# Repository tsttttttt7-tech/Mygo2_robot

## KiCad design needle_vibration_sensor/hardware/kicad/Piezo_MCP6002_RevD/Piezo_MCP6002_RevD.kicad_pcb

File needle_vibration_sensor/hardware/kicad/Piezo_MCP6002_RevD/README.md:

# Piezo MCP6002 - Rev D PCB project

Same style as Rev C (self-contained symbols/footprints, routed 2-layer board, DRC, BOM, previews), with the Rev D circuit.

## Open in KiCad
1. Extract the whole ZIP into one folder.
2. Open `Piezo_MCP6002_RevD.kicad_pro` in KiCad 7 or newer.
3. Open the schematic and the PCB from the project tree. If you edit copper, press **B** to refill the zones.

Keep `Piezo_PCB.pretty`, `Piezo_Local.kicad_sym`, `fp-lib-table` and `sym-lib-table` with the project.

## What is included
- Routed two-layer PCB, **48 × 32 mm** (Rev C: 70 × 45 mm), 1.6 mm.
- **All signal tracks on the top layer.** The bottom layer is an unbroken GND plane (best shielding for the high-impedance piezo input). GND pour on top as well.
- 33 components, 0.25 mm tracks, 0.6/0.3 mm vias (8 GND vias next to the SMD GND pads + about 90 stitching vias).
- `Schematic.pdf`, `PCB_top_preview`, `PCB_bottom_preview`, `PCB_routing_preview` (pours hidden), `PCB_assembly` (PNG + PDF).
- `Gerbers_Piezo_MCP6002_RevD.zip`: copper, mask, silk, paste, outline and Excellon drill. Ready to upload to JLCPCB / PCBWay.
- `BOM.csv`, `DRC.txt`, `Validation.txt`, `Connectivity.txt`.

## Changes from Rev C
| | Rev C | Rev D |
|---|---|---|
| Low-pass | 9.9 kHz, E96 values (14.7 k, 6.19 k) | **15 kHz**; every R and C taken from the Ardunic 1206 kits ARD-065066 / ARD-065072 (12k/390k/470p/47p, 33k/200k/470p/33p) |
| C1 (1 µF film input cap) | yes | **removed**: the piezo already blocks DC |
| Input clamp | BAV199 | **BAV99** (same SOT-23 pinout, in stock at Al-Hekmh) |
| Gain | fixed 11 | **11 with JP1 bridged / 44 with JP1 open** (R4 1 k, R3 10 k + R14 33 k) |
| Stability | – | C5 47 pF across the feedback network |
| Outputs | J3 only | **J3 OUT_DC** (ESP32-S3 ADC, via R7/C6) + **J4 OUT_AC** (PCM1808, via C7/R13) |
| Supply filter | R12 22 Ω, C3 47 µF | R12 10 Ω, C3 22 µF |
| Input bias | R2 4.7 MΩ (corner ~3 Hz) | R2 1 MΩ (corner ~16 Hz), the kit's largest value |

## Connectors
| Connector | Pin 1 (square pad) | Pin 2 |
|---|---|---|
| J1 | Piezo ceramic (+) | Piezo brass / GND |
| J2 | Regulated 3.3 V from the ESP32 board | GND |
| J3 | OUT_DC, biased at 1.65 V, to ESP32-S3 GPIO1 | GND |
| J4 | OUT_AC to PCM1808 `L` | GND |

## Assembly notes
- **JP1:** bridge the two pads with solder for gain 11 (start here). Remove the bridge for gain 44.
- U1/U2 are DIP-8 (MCP6002-I/P from Al-Hekmh). Sockets are optional, but they add height (see the housing).
- Filter capacitors C5, C8–C11 are the pF values of the kit (C0G/NP0 dielectric, stable).
- Clean the flux well around the high-impedance nodes: R1/R2/D1/U1 pin 3 (input) and R9 (390k) / R11 (200k) with C9/C11 (filter).
- Three reference labels (C6, R10, R14) had no free silkscreen spot. They are on the assembly (F.Fab) layer: see `PCB_assembly.png`.
- Housing for this board: `../../stl/revD_48x32/` (58 × 42 mm body). Trim the through-hole leads to ≤ 1 mm under the board, because the cover lip leaves 1 mm.

## Validation
KiCad 7.0.11. DRC: **0 violations, 0 unconnected pads, 0 footprint errors**, with the Rev C project rules
(0.2 mm clearance, 0.5 mm copper-to-edge, 0.8 mm silk text). All 79 pad nets and 33 values/footprints match the schematic
netlist exported by KiCad itself (`Validation.txt`). No ERC (not available in kicad-cli 7), and no hardware test yet.

## Regenerate
Everything is produced by scripts in `../tools/` (`design.py` = the netlist):
`bash tools/build_all.sh` (add `--place` to re-run placement). Routing uses a custom 2-layer grid router, then KiCad fills the zones and runs DRC.

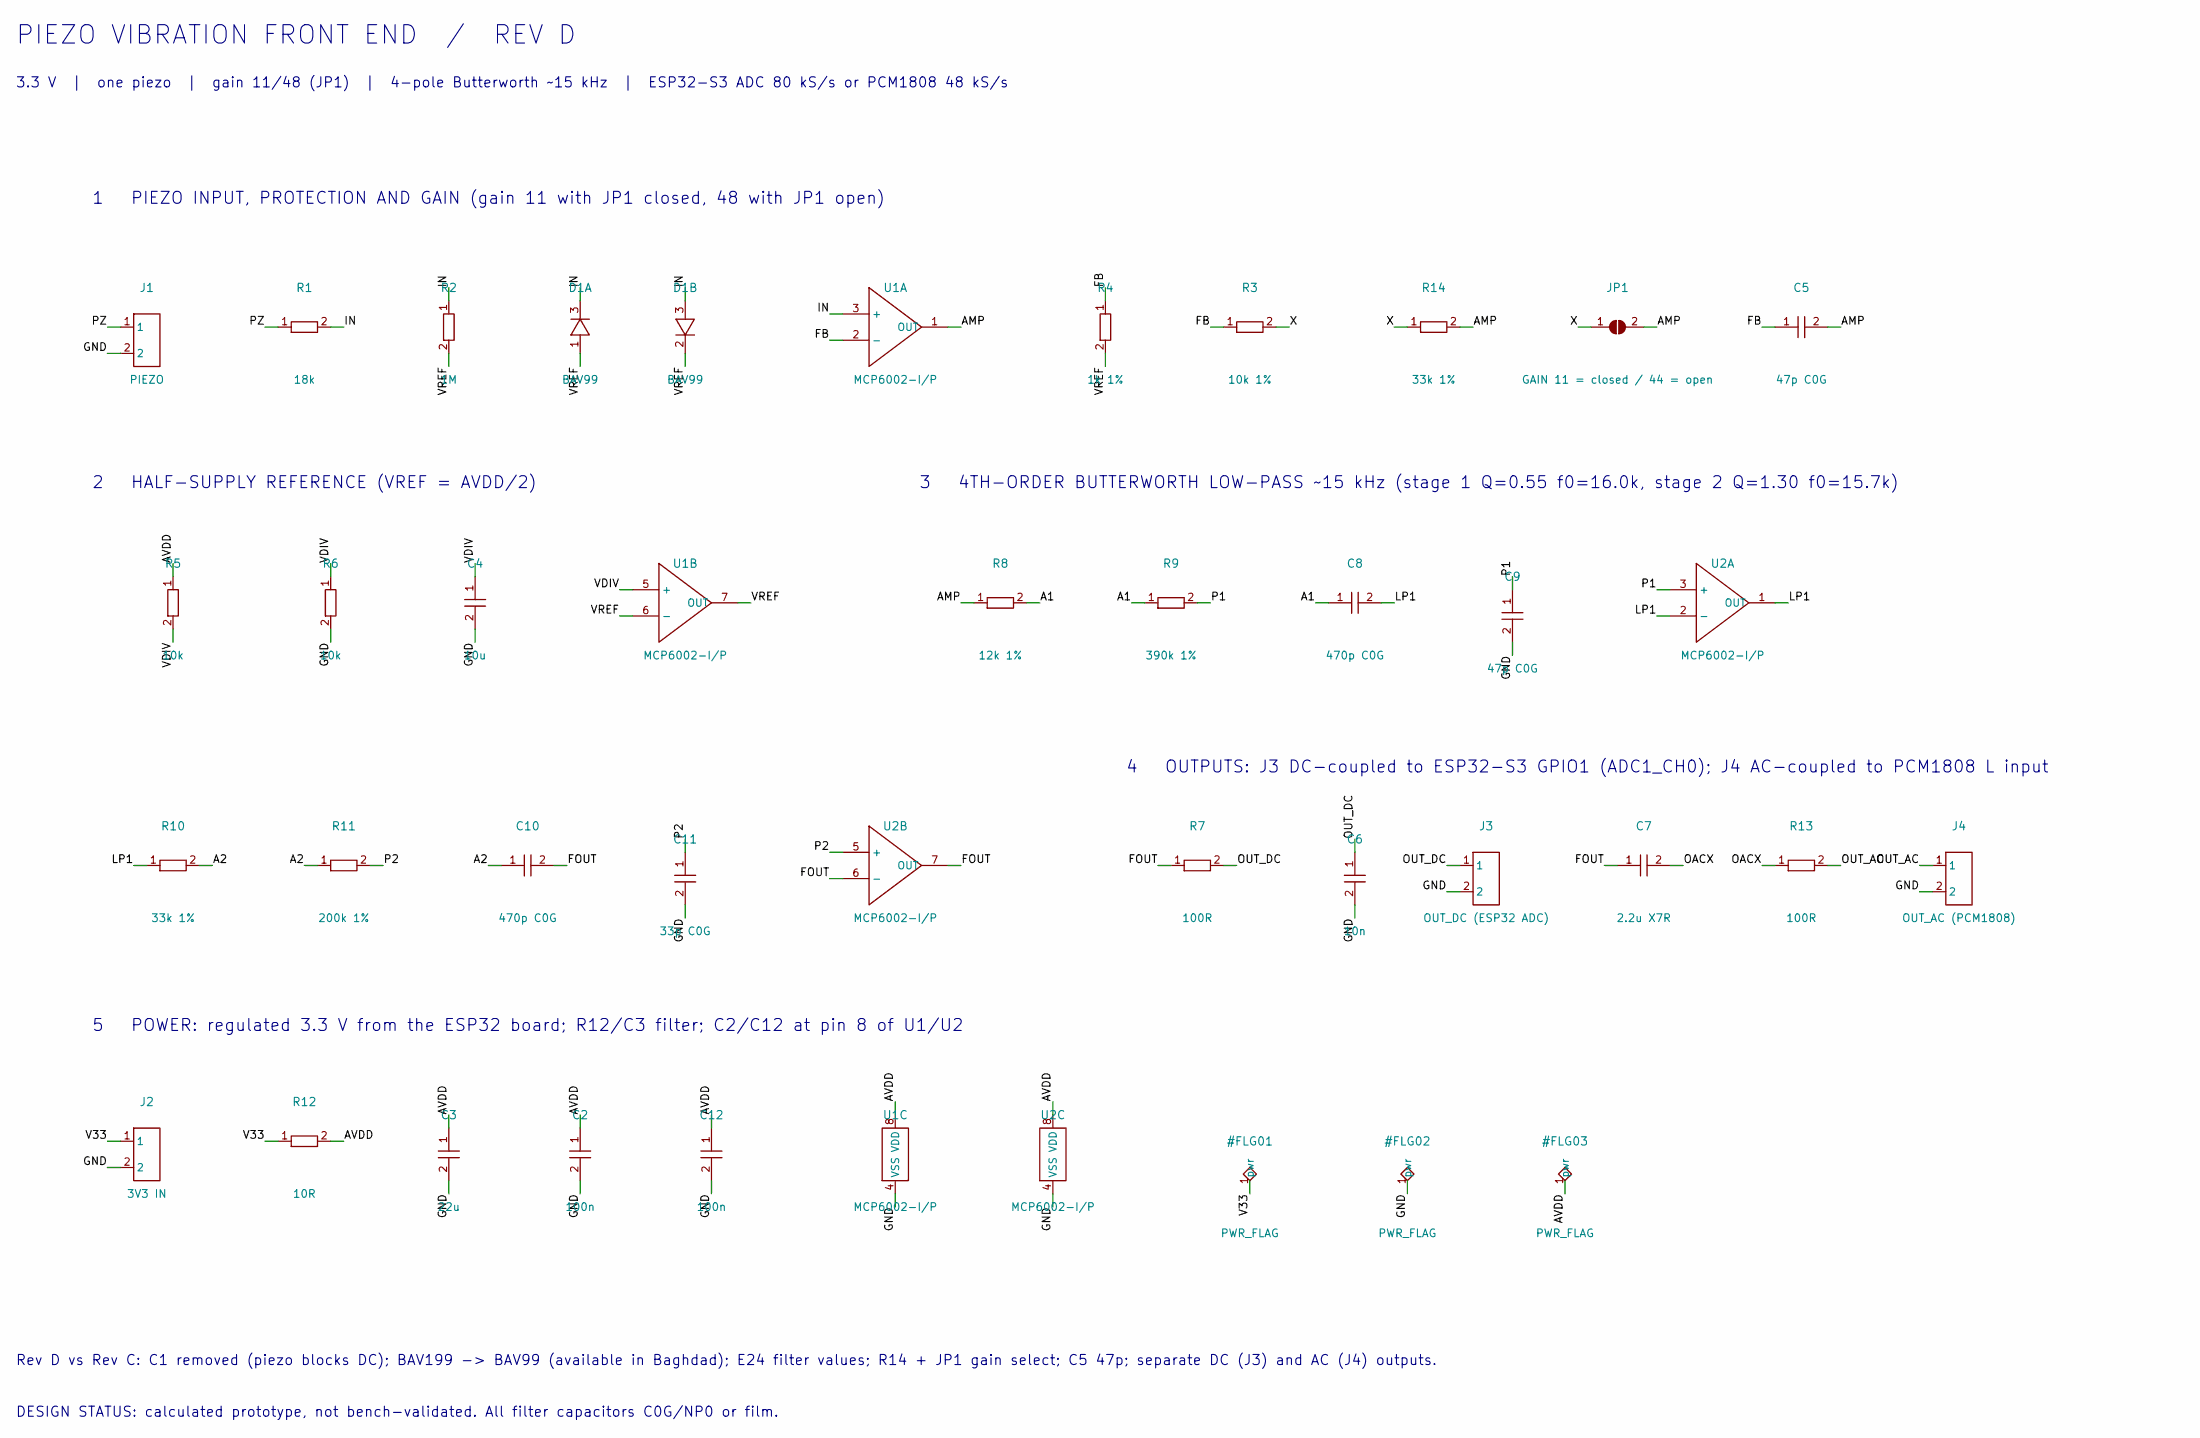
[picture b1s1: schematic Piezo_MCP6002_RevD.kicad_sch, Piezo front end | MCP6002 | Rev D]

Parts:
C2, C12: 100n; C1206
C3: 22u; C1206
C4: 10u; C1206
C5, C9: 47p C0G; C1206
C6: 10n; C1206
C7: 2.2u X7R; C1206
C8, C10: 470p C0G; C1206
C11: 33p C0G; C1206
D1: BAV99; BAV99_SOT23
J1: PIEZO; Header_1x02
J2: 3V3 IN; Header_1x02
J3: OUT_DC (ESP32 ADC); Header_1x02
J4: OUT_AC (PCM1808); Header_1x02
JP1: GAIN 11 = closed / 44 = open; SolderJumper_2
R1: 18k; R1206
R2: 1M; R1206
R3: 10k 1%; R1206
R4: 1k 1%; R1206
R5, R6: 10k; R1206
R7, R13: 100R; R1206
R8: 12k 1%; R1206
R9: 390k 1%; R1206
R10, R14: 33k 1%; R1206
R11: 200k 1%; R1206
R12: 10R; R1206
U1, U2: MCP6002-I/P; DIP8

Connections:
A1: C8.1, R8.2, R9.1
A2: C10.1, R10.2, R11.1
AMP: C5.2, JP1.2, R8.1, R14.2, U1.1 (OUT)
AVDD: C2.1, C3.1, C12.1, R5.1, R12.2, U1.8 (VDD), U2.8 (VDD)
FB: C5.1, R3.1, R4.1, U1.2 (-)
FOUT: C7.1, C10.2, R7.1, U2.6 (-), U2.7 (OUT)
GND: C2.2, C3.2, C4.2, C6.2, C9.2, C11.2, C12.2, J1.2, J2.2, J3.2, J4.2, R6.2, U1.4 (VSS), U2.4 (VSS)
IN: D1.3 (K1/A2), R1.2, R2.1, U1.3 (+)
LP1: C8.2, R10.1, U2.1 (OUT), U2.2 (-)
OACX: C7.2, R13.1
OUT_AC: J4.1, R13.2
OUT_DC: C6.1, J3.1, R7.2
P1: C9.1, R9.2, U2.3 (+)
P2: C11.1, R11.2, U2.5 (+)
PZ: J1.1, R1.1
V33: J2.1, R12.1
VDIV: C4.1, R5.2, R6.1, U1.5 (+)
VREF: D1.1 (A1), D1.2 (K2), R2.2, R4.2, U1.6 (-), U1.7 (OUT)
X: JP1.1, R3.2, R14.1

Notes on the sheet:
1 PIEZO INPUT, PROTECTION AND GAIN (gain 11 with JP1 closed, 48 with JP1 open)
2 HALF-SUPPLY REFERENCE (VREF = AVDD/2)
3 4TH-ORDER BUTTERWORTH LOW-PASS ~15 kHz (stage 1 Q=0.55 f0=16.0k, stage 2 Q=1.30 f0=15.7k)
4 OUTPUTS: J3 DC-coupled to ESP32-S3 GPIO1 (ADC1_CH0); J4 AC-coupled to PCM1808 L input
5 POWER: regulated 3.3 V from the ESP32 board; R12/C3 filter; C2/C12 at pin 8 of U1/U2
PIEZO VIBRATION FRONT END / REV D
3.3 V | one piezo | gain 11/48 (JP1) | 4-pole Butterworth ~15 kHz | ESP32-S3 ADC 80 kS/s or PCM1808 48 kS/s
Rev D vs Rev C: C1 removed (piezo blocks DC); BAV199 -> BAV99 (available in Baghdad); E24 filter values; R14 + JP1 gain select; C5 47p; separate DC (J3) and AC (J4) outputs.
DESIGN STATUS: calculated prototype, not bench-validated. All filter capacitors C0G/NP0 or film.

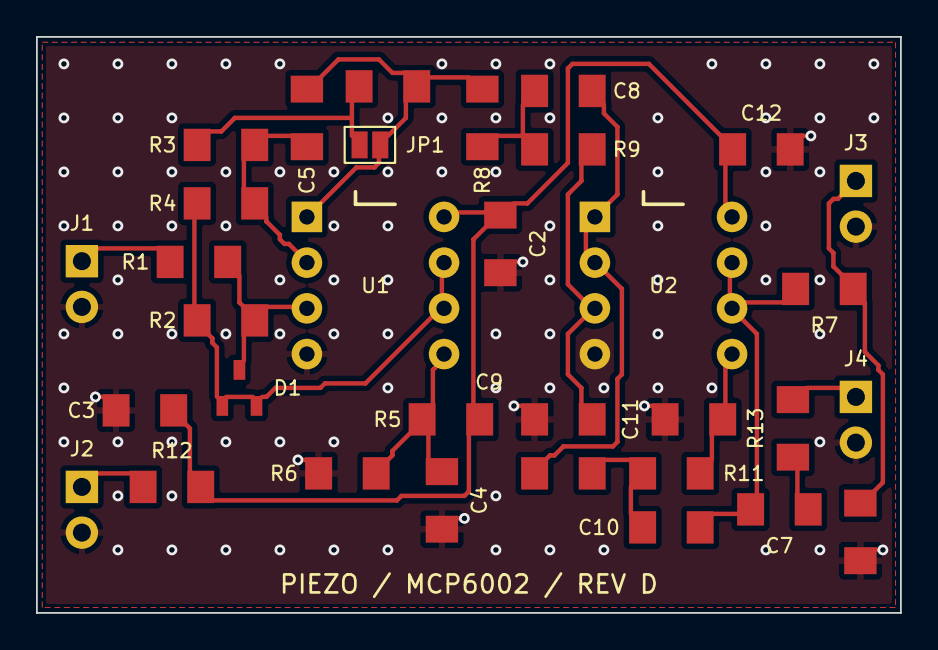
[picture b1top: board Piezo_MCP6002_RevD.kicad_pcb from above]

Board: 2 copper layers, 48.0 x 32.0 mm, 33 parts (0 on the bottom side), 19 nets.

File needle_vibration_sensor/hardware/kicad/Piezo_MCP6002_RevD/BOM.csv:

Reference,Value,Footprint,Package note,Baghdad source
C2,100n,Piezo_PCB:C1206,1206 SMD,"Ardunic capacitor kit ARD-065072 (1206, 16 values, IQD 7,000)"
C3,22u,Piezo_PCB:C1206,1206 SMD,"Ardunic capacitor kit ARD-065072 (1206, 16 values, IQD 7,000)"
C4,10u,Piezo_PCB:C1206,1206 SMD,"Ardunic capacitor kit ARD-065072 (1206, 16 values, IQD 7,000)"
C5,47p C0G,Piezo_PCB:C1206,1206 SMD,"Ardunic capacitor kit ARD-065072 (1206, 16 values, IQD 7,000)"
C6,10n,Piezo_PCB:C1206,1206 SMD,"Ardunic capacitor kit ARD-065072 (1206, 16 values, IQD 7,000)"
C7,2.2u X7R,Piezo_PCB:C1206,1206 SMD,"Ardunic capacitor kit ARD-065072 (1206, 16 values, IQD 7,000)"
C8,470p C0G,Piezo_PCB:C1206,1206 SMD,"Ardunic capacitor kit ARD-065072 (1206, 16 values, IQD 7,000)"
C9,47p C0G,Piezo_PCB:C1206,1206 SMD,"Ardunic capacitor kit ARD-065072 (1206, 16 values, IQD 7,000)"
C10,470p C0G,Piezo_PCB:C1206,1206 SMD,"Ardunic capacitor kit ARD-065072 (1206, 16 values, IQD 7,000)"
C11,33p C0G,Piezo_PCB:C1206,1206 SMD,"Ardunic capacitor kit ARD-065072 (1206, 16 values, IQD 7,000)"
C12,100n,Piezo_PCB:C1206,1206 SMD,"Ardunic capacitor kit ARD-065072 (1206, 16 values, IQD 7,000)"
D1,BAV99,Piezo_PCB:BAV99_SOT23,"SOT-23; pin 3 = IN, pins 1+2 = VREF","Al-Hekmh Electronics, Tahrir Sq. (alhekmh.com)"
J1,PIEZO,Piezo_PCB:Header_1x02,2.54 mm 2-pin header,any component shop
J2,3V3 IN,Piezo_PCB:Header_1x02,2.54 mm 2-pin header,any component shop
J3,OUT_DC (ESP32 ADC),Piezo_PCB:Header_1x02,2.54 mm 2-pin header,any component shop
J4,OUT_AC (PCM1808),Piezo_PCB:Header_1x02,2.54 mm 2-pin header,any component shop
JP1,GAIN 11 = closed / 44 = open,Piezo_PCB:SolderJumper_2,"solder bridge = gain 11, open = gain 44","PCB pads, no part"
R1,18k,Piezo_PCB:R1206,1206 SMD 1 %,"Ardunic resistor kit ARD-065066 (1206, 33 values, IQD 7,500)"
R2,1M,Piezo_PCB:R1206,1206 SMD 1 %,"Ardunic resistor kit ARD-065066 (1206, 33 values, IQD 7,500)"
R3,10k 1%,Piezo_PCB:R1206,1206 SMD 1 %,"Ardunic resistor kit ARD-065066 (1206, 33 values, IQD 7,500)"
R4,1k 1%,Piezo_PCB:R1206,1206 SMD 1 %,"Ardunic resistor kit ARD-065066 (1206, 33 values, IQD 7,500)"
R5,10k,Piezo_PCB:R1206,1206 SMD 1 %,"Ardunic resistor kit ARD-065066 (1206, 33 values, IQD 7,500)"
R6,10k,Piezo_PCB:R1206,1206 SMD 1 %,"Ardunic resistor kit ARD-065066 (1206, 33 values, IQD 7,500)"
R7,100R,Piezo_PCB:R1206,1206 SMD 1 %,"Ardunic resistor kit ARD-065066 (1206, 33 values, IQD 7,500)"
R8,12k 1%,Piezo_PCB:R1206,1206 SMD 1 %,"Ardunic resistor kit ARD-065066 (1206, 33 values, IQD 7,500)"
R9,390k 1%,Piezo_PCB:R1206,1206 SMD 1 %,"Ardunic resistor kit ARD-065066 (1206, 33 values, IQD 7,500)"
R10,33k 1%,Piezo_PCB:R1206,1206 SMD 1 %,"Ardunic resistor kit ARD-065066 (1206, 33 values, IQD 7,500)"
R11,200k 1%,Piezo_PCB:R1206,1206 SMD 1 %,"Ardunic resistor kit ARD-065066 (1206, 33 values, IQD 7,500)"
R12,10R,Piezo_PCB:R1206,1206 SMD 1 %,"Ardunic resistor kit ARD-065066 (1206, 33 values, IQD 7,500)"
R13,100R,Piezo_PCB:R1206,1206 SMD 1 %,"Ardunic resistor kit ARD-065066 (1206, 33 values, IQD 7,500)"
R14,33k 1%,Piezo_PCB:R1206,1206 SMD 1 %,"Ardunic resistor kit ARD-065066 (1206, 33 values, IQD 7,500)"
U1,MCP6002-I/P,Piezo_PCB:DIP8,"DIP-8, 7.62 mm rows; socket optional","Al-Hekmh Electronics, Tahrir Sq. (alhekmh.com)"
U2,MCP6002-I/P,Piezo_PCB:DIP8,"DIP-8, 7.62 mm rows; socket optional","Al-Hekmh Electronics, Tahrir Sq. (alhekmh.com)"

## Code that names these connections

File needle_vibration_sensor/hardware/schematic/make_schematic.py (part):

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    # ======================= VREF (U1B) =======================
    X0, Y0 = 0, -6.5
    d.add(elm.Label().at((X0, Y0 + 2.6)).label('2) Half-supply reference', fontsize=12, halign='left'))
    d.add(elm.Vdd().at((X0 + 1.2, Y0 + 1.6)).label('AVDD', fontsize=FS))
    d.add(elm.Resistor().down().label('R5\n10k', loc='bottom', fontsize=FS))
    nd = d.add(elm.Dot().label('VDIV', loc='left', fontsize=8))
    d.add(elm.Resistor().down().label('R6\n10k', loc='bottom', fontsize=FS))
    d.add(elm.Ground())
    d.add(elm.Line().at(nd.center).right().length(1.4))
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    d.add(elm.Line().at((PX + 0.5, PY + 0.5)).right().length(0.5))
    d.add(elm.Resistor().right().label('R12 10Ω', fontsize=FS))
    na = d.add(elm.Dot())
    d.add(elm.Vdd().at(na.center).label('AVDD', fontsize=FS))
    for name in ['C3\n22µ', 'C2\n100n\n(U1 pin8)', 'C12\n100n\n(U2 pin8)']:
        d.add(elm.Line().at(na.center).right().length(1.6))
        na = d.add(elm.Dot())
        d.add(elm.Capacitor().down().at(na.center).label(name, loc='bottom', fontsize=FS))
        d.add(elm.Ground())
    d.add(elm.Label().at((PX, PY - 3.0)).label(
        'J3: OUT_DC → ESP32-S3 GPIO1 (ADC1_CH0)      J4: OUT_AC → PCM1808 "L"\n'
        'U1, U2 = MCP6002 (pin 8 = AVDD, pin 4 = GND)    values from Ardunic 1206 kits ARD-065066 / ARD-065072',
        fontsize=9, halign='left'))

    # ======================= FILTER (U2A, U2B) =======================
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    nf = d.add(elm.Dot())
    d.add(elm.Resistor().right().label('R7 100Ω', fontsize=FS))
    nj3 = d.add(elm.Dot())
    d.add(elm.Line().right().length(1.0).label('J3 OUT_DC', loc='right', fontsize=FS))
    d.add(elm.Capacitor().down().at(nj3.center).label('C6\n10n', loc='bottom', fontsize=FS))
    d.add(elm.Ground())
    d.add(elm.Line().at(nf.center).down().length(3.0))
    d.add(elm.Capacitor().right().label('C7 2.2µ', loc='bottom', fontsize=FS))
    d.add(elm.Resistor().right().label('R13 100Ω', loc='bottom', fontsize=FS))
    d.add(elm.Line().right().length(1.0).label('J4 OUT_AC', loc='right', fontsize=FS))

    d.add(elm.Label().at((0, -21.5)).label(
        'Piezo needle sensor - amplifier + filter, Rev D (Mygo2_robot)      gain 11 (JP1 closed) / 44 (open), '
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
